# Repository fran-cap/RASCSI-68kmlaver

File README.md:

# RASCSI-68kmlaver
A scsi emulator based off of the work of http://www.geocities.jp/kugimoto0715/rascsi/index.html

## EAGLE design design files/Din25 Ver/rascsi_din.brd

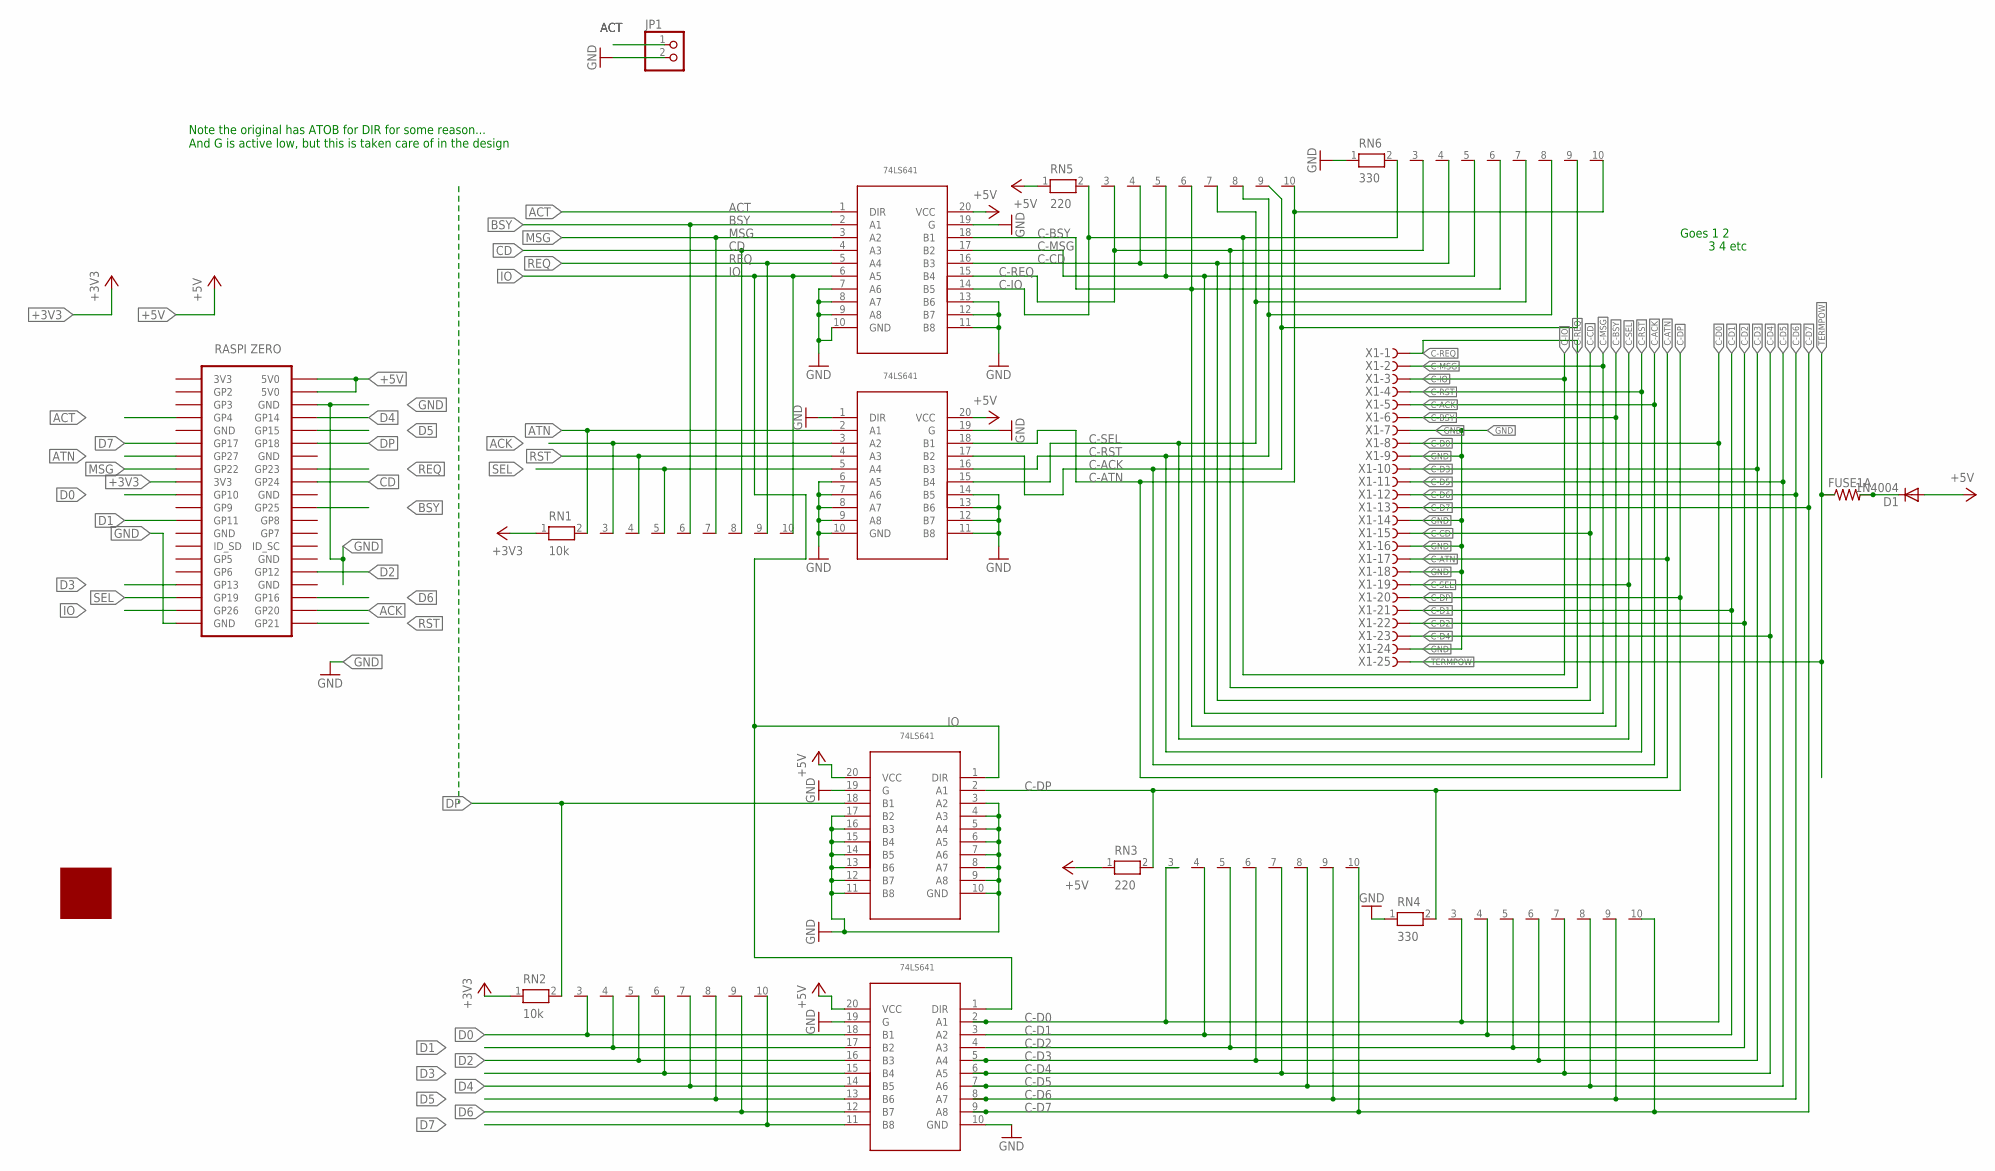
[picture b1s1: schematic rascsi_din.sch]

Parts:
D1: 1N4004; DO41-10
FUSE1A: R-US_0204/7; 0204/7
JP1: PINHD-1X2; 1X02
RN1, RN2: 10k; RN-10
RN3, RN5: 220; RN-10
RN4, RN6: 330; RN-10
U11, U22, U33, U44: SN74LS641-1SC; SOIC20S
U$1: ZERO
U$2: LOGO
X1: F25HPS; F25HP

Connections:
+3V3: RN1.1, RN2.1, U$1.17 (3V3)
+5V: D1.A, RN3.1, RN5.1, U11.20 (VCC), U22.20 (VCC), U33.20 (VCC), U44.20 (VCC), U$1.2 (5V0), U$1.4 (5V0)
ACK: RN1.3, U22.3 (A2), U$1.38 (GP20)
ACT: JP1.1, U11.1 (DIR), U$1.7 (GP4)
ATN: RN1.2, U22.2 (A1), U$1.13 (GP27)
BSY: RN1.6, U11.2 (A1), U$1.22 (GP25)
C-ACK: RN5.9, RN6.9, U22.17 (B2), X1.5
C-ATN: RN5.10, RN6.10, U22.18 (B1), X1.17
C-BSY: RN5.6, RN6.6, U11.18 (B1), X1.6
C-CD: RN5.4, RN6.4, U11.16 (B3), X1.15
C-D0: RN3.3, RN4.3, U44.2 (A1), X1.8
C-D1: RN3.4, RN4.4, U44.3 (A2), X1.21
C-D2: RN3.5, RN4.5, U44.4 (A3), X1.22
C-D3: RN3.6, RN4.6, U44.5 (A4), X1.10
C-D4: RN3.7, RN4.7, U44.6 (A5), X1.23
C-D5: RN3.8, RN4.8, U44.7 (A6), X1.11
C-D6: RN3.9, RN4.9, U44.8 (A7), X1.12
C-D7: RN3.10, RN4.10, U44.9 (A8), X1.13
C-DP: RN3.2, RN4.2, U33.2 (A1), X1.20
C-IO: RN5.2, RN6.2, U11.14 (B5), X1.3
C-MSG: RN5.5, RN6.5, U11.17 (B2), X1.2
C-REQ: RN5.3, RN6.3, U11.15 (B4), X1.1
C-RST: RN5.8, RN6.8, U22.16 (B3), X1.4
C-SEL: RN5.7, RN6.7, U22.15 (B4), X1.19
CD: RN1.8, U11.4 (A3), U$1.18 (GP24)
D0: RN2.3, U44.18 (B1), U$1.19 (GP10)
D1: RN2.4, U44.17 (B2), U$1.23 (GP11)
D2: RN2.5, U44.16 (B3), U$1.32 (GP12)
D3: RN2.6, U44.15 (B4), U$1.33 (GP13)
D4: RN2.7, U44.14 (B5), U$1.8 (GP14)
D5: RN2.8, U44.13 (B6), U$1.10 (GP15)
D6: RN2.9, U44.12 (B7), U$1.36 (GP16)
D7: RN2.10, U44.11 (B8), U$1.11 (GP17)
DP: RN2.2, U33.18 (B1), U$1.12 (GP18)
GND: JP1.2, RN4.1, RN6.1, U11.7 (A6), U11.8 (A7), U11.9 (A8), U11.10 (GND), U11.11 (B8), U11.12 (B7), U11.13 (B6), U11.19 (G), U22.1 (DIR), U22.6 (A5), U22.7 (A6), U22.8 (A7), U22.9 (A8), U22.10 (GND), U22.11 (B8), U22.12 (B7), U22.13 (B6), U22.14 (B5), U22.19 (G), U33.3 (A2), U33.4 (A3), U33.5 (A4), U33.6 (A5), U33.7 (A6), U33.8 (A7), U33.9 (A8), U33.10 (GND), U33.11 (B8), U33.12 (B7), U33.13 (B6), U33.14 (B5), U33.15 (B4), U33.16 (B3), U33.17 (B2), U33.19 (G), U44.10 (GND), U44.19 (G), U$1.6 (GND), U$1.39 (GND), X1.7, X1.9, X1.14, X1.16, X1.18, X1.24
IO: RN1.10, U11.6 (A5), U33.1 (DIR), U44.1 (DIR), U$1.37 (GP26)
MSG: RN1.7, U11.3 (A2), U$1.15 (GP22)
unnamed: D1.C, FUSE1A.2
REQ: RN1.9, U11.5 (A4), U$1.16 (GP23)
RST: RN1.4, U22.4 (A3), U$1.40 (GP21)
SEL: RN1.5, U22.5 (A4), U$1.35 (GP19)
TERMPOW: FUSE1A.1, X1.25

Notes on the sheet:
Note the original has ATOB for DIR for some reason... And G is active low, but this is taken care of in the design
Goes 1 2
3 4 etc

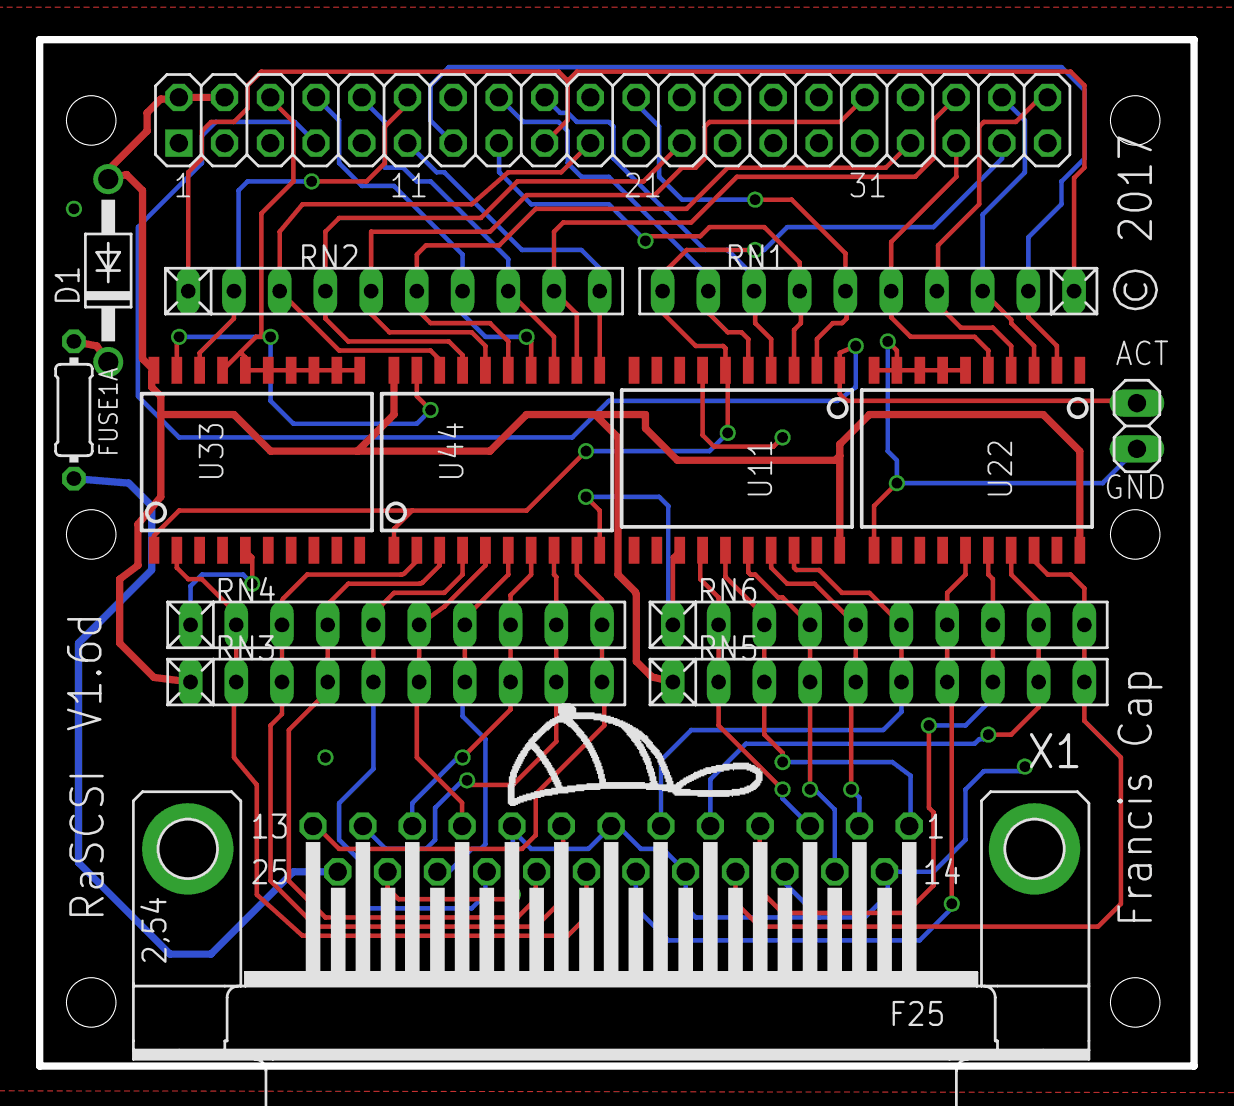
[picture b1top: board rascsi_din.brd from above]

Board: 2 copper layers, 64.1 x 57.0 mm, 16 parts (0 on the bottom side), 42 nets.

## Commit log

2017-11-14 Base upload of all files
    Just getting everything up. Readme on information eta.
2017-11-19 New boards
    Shrunk internal board down to min size. Also added a din25 board for external use.

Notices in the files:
design files/Din25 Ver/rascsi_din.brd:
© 2017
